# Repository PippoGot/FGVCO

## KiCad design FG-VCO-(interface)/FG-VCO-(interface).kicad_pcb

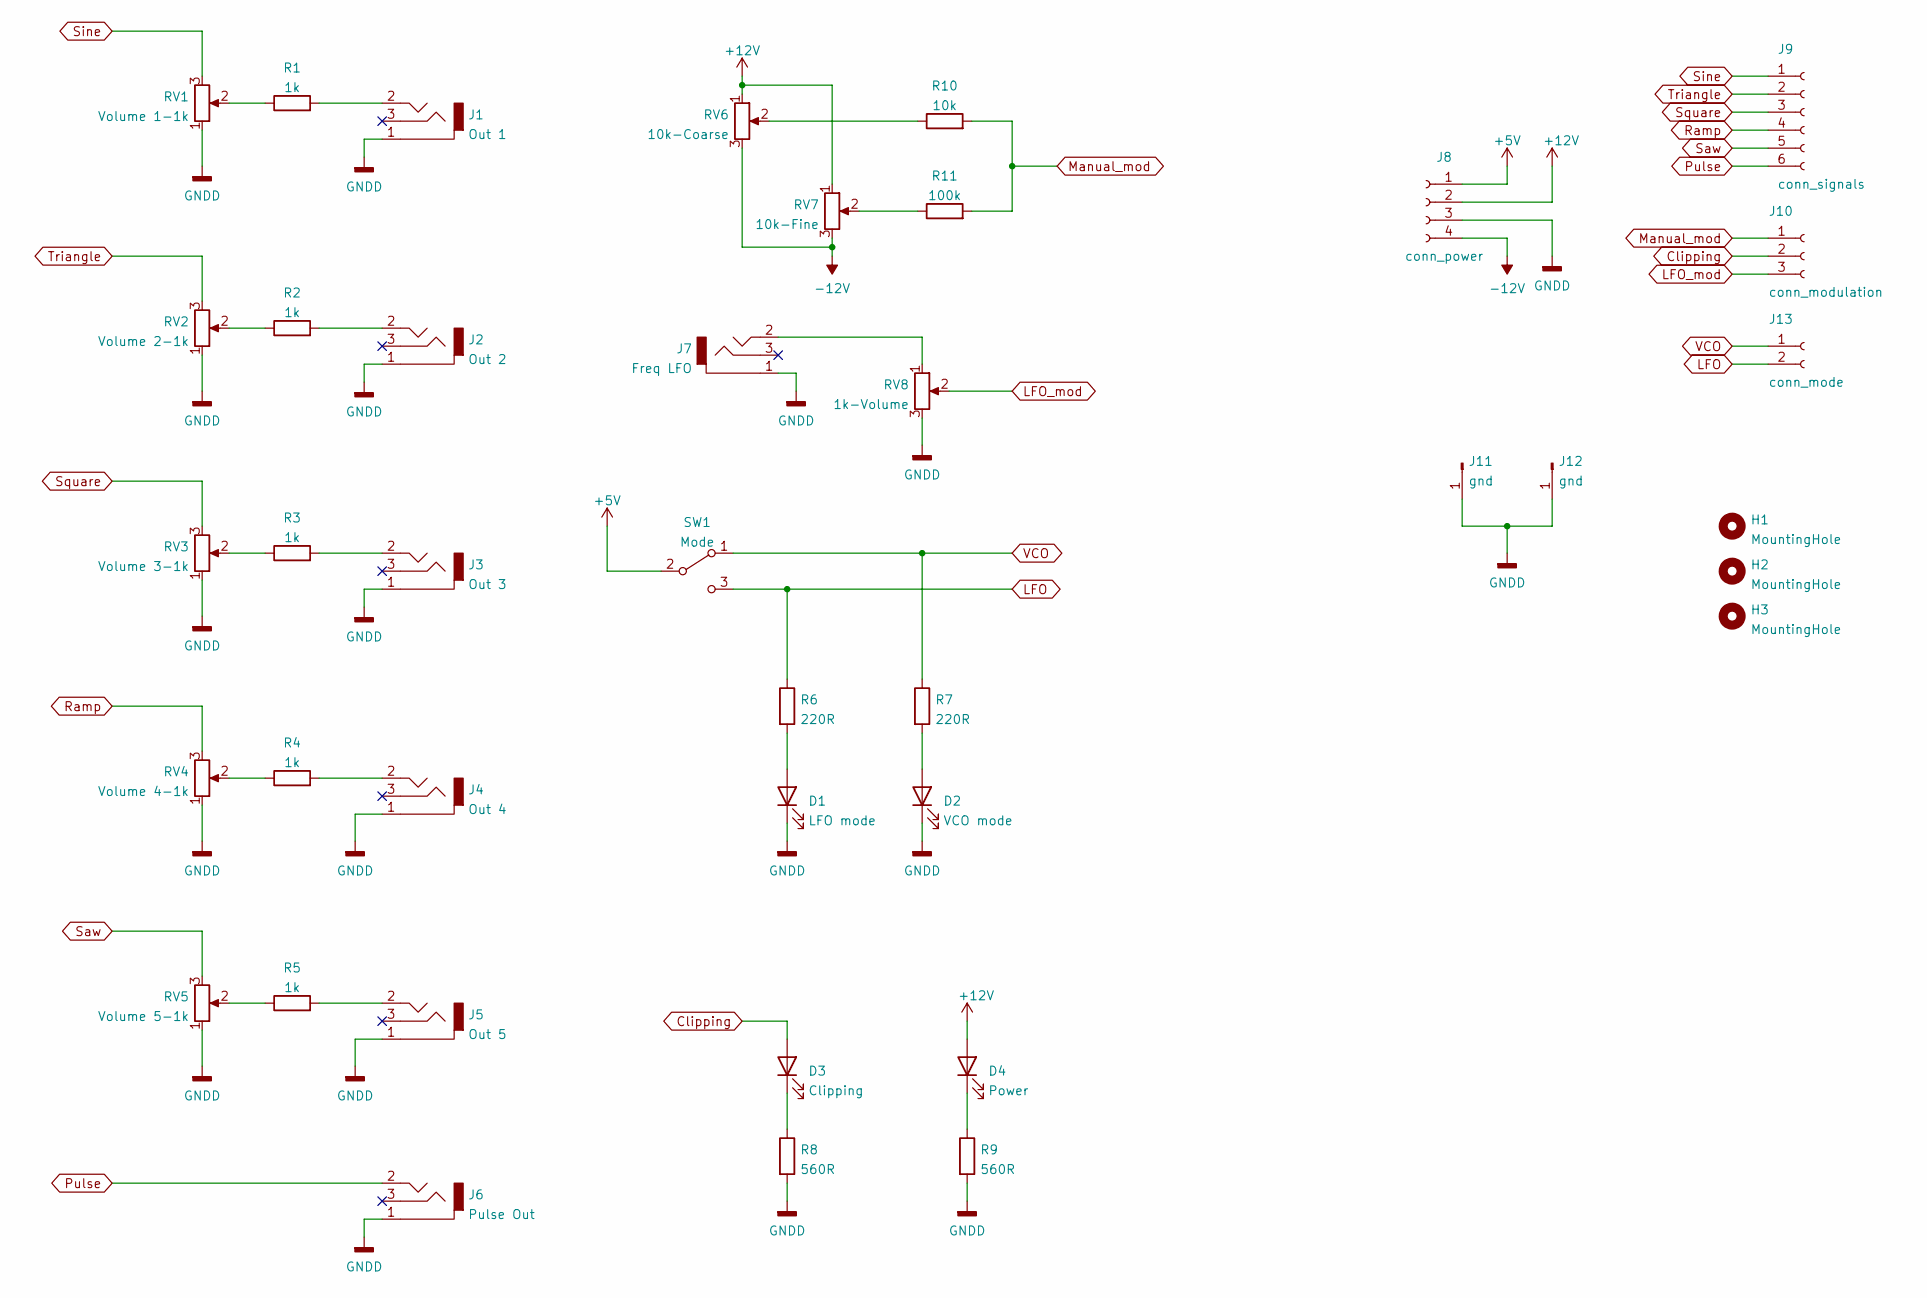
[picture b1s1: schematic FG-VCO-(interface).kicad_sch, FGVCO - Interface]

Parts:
D1: LFO mode; LED_D3.0mm_FlatTop
D2: VCO mode; LED_D3.0mm_FlatTop
D3: Clipping; LED_D3.0mm_FlatTop
D4: Power; LED_D3.0mm_FlatTop
H1, H2, H3: MountingHole; MountingHole_3.2mm_M3
J1: Out 1; PJ_301M_noGND
J2: Out 2; PJ_301M_noGND
J3: Out 3; PJ_301M_noGND
J4: Out 4; PJ_301M_noGND
J5: Out 5; PJ_301M_noGND
J6: Pulse Out; PJ_301M_noGND
J7: Freq LFO; PJ_301M_noGND
J8: conn_power; PinSocket_1x04_P2.54mm_Vertical
J9: conn_signals; PinSocket_1x06_P2.54mm_Vertical
J10: conn_modulation; PinSocket_1x03_P2.54mm_Vertical
J11, J12: gnd; PinSocket_1x01_P2.54mm_Vertical
J13: conn_mode; PinSocket_1x02_P2.54mm_Vertical
R1, R2, R3, R4, R5: 1k; R_Axial_DIN0207_L6.3mm_D2.5mm_P10.16mm_Horizontal
R6, R7: 220R; R_Axial_DIN0207_L6.3mm_D2.5mm_P10.16mm_Horizontal
R8, R9: 560R; R_Axial_DIN0207_L6.3mm_D2.5mm_P10.16mm_Horizontal
R10: 10k; R_Axial_DIN0207_L6.3mm_D2.5mm_P10.16mm_Horizontal
R11: 100k; R_Axial_DIN0207_L6.3mm_D2.5mm_P10.16mm_Horizontal
RV1: Volume 1-1k; RV-90 Potentiometer
RV2: Volume 2-1k; RV-90 Potentiometer
RV3: Volume 3-1k; RV-90 Potentiometer
RV4: Volume 4-1k; RV-90 Potentiometer
RV5: Volume 5-1k; RV-90 Potentiometer
RV6: 10k-Coarse; RV-90 Potentiometer
RV7: 10k-Fine; RV-90 Potentiometer
RV8: 1k-Volume; RV-90 Potentiometer
SW1: Mode; SPDT Switch

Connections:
+5V: J8.1, SW1.2 (B)
+12V: D4.2 (A), J8.2, RV6.1, RV7.1
-12V: J8.4, RV6.3, RV7.3
Clipping: D3.2 (A), J10.2
GNDD: D1.1 (K), D2.1 (K), J1.1, J2.1, J3.1, J4.1, J5.1, J6.1, J7.1, J8.3, J11.1, J12.1, R8.2, R9.2, RV1.1, RV2.1, RV3.1, RV4.1, RV5.1, RV8.3
LFO: J13.2, R6.1, SW1.3 (C)
LFO_mod: J10.3, RV8.2
Manual_mod: J10.1, R10.2, R11.2
unnamed: D1.2 (A), R6.2
unnamed: D2.2 (A), R7.2
unnamed: D3.1 (K), R8.1
unnamed: D4.1 (K), R9.1
unnamed: J1.2, R1.2
unnamed: J2.2, R2.2
unnamed: J3.2, R3.2
unnamed: J4.2, R4.2
unnamed: J5.2, R5.2
unnamed: J7.2, RV8.1
unnamed: R1.1, RV1.2
unnamed: R2.1, RV2.2
unnamed: R3.1, RV3.2
unnamed: R4.1, RV4.2
unnamed: R5.1, RV5.2
unnamed: R10.1, RV6.2
unnamed: R11.1, RV7.2
Pulse: J6.2, J9.6
Ramp: J9.4, RV4.3
Saw: J9.5, RV5.3
Sine: J9.1, RV1.3
Square: J9.3, RV3.3
Triangle: J9.2, RV2.3
VCO: J13.1, R7.1, SW1.1 (A)

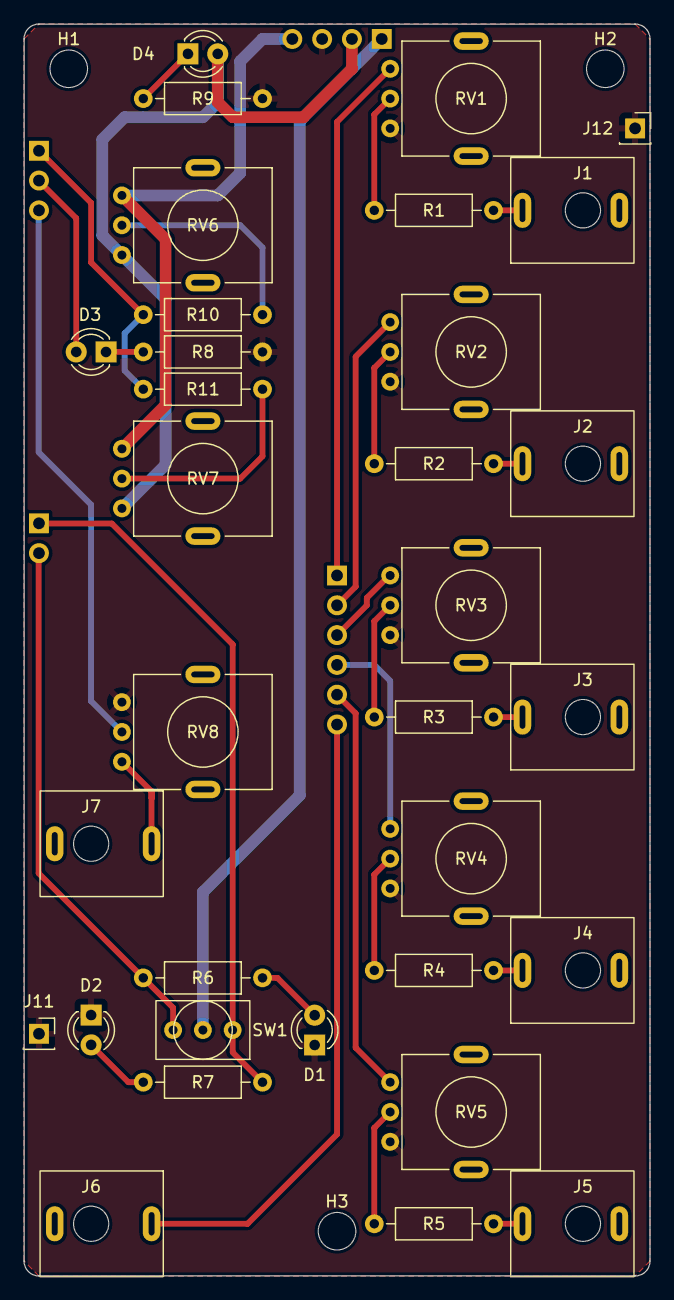
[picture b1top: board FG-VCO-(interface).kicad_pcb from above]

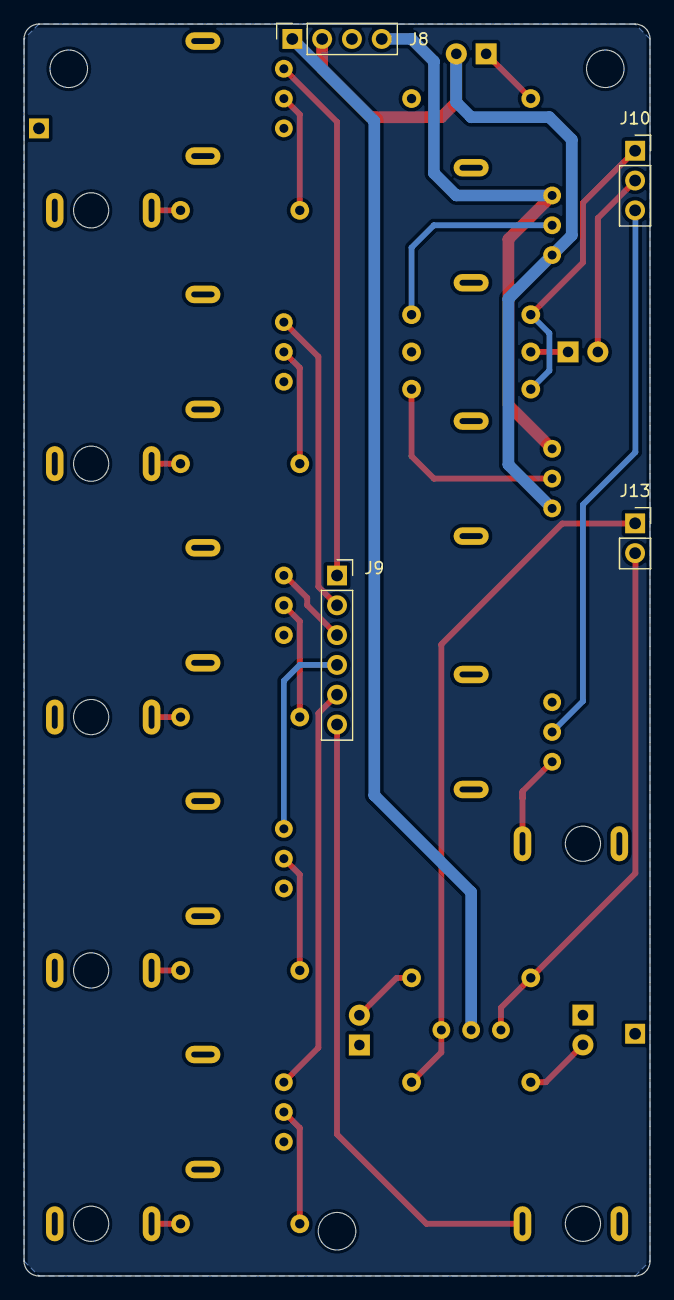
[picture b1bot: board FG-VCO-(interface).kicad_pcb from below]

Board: 2 copper layers, 53.3 x 106.7 mm, 40 parts (4 on the bottom side), 32 nets.

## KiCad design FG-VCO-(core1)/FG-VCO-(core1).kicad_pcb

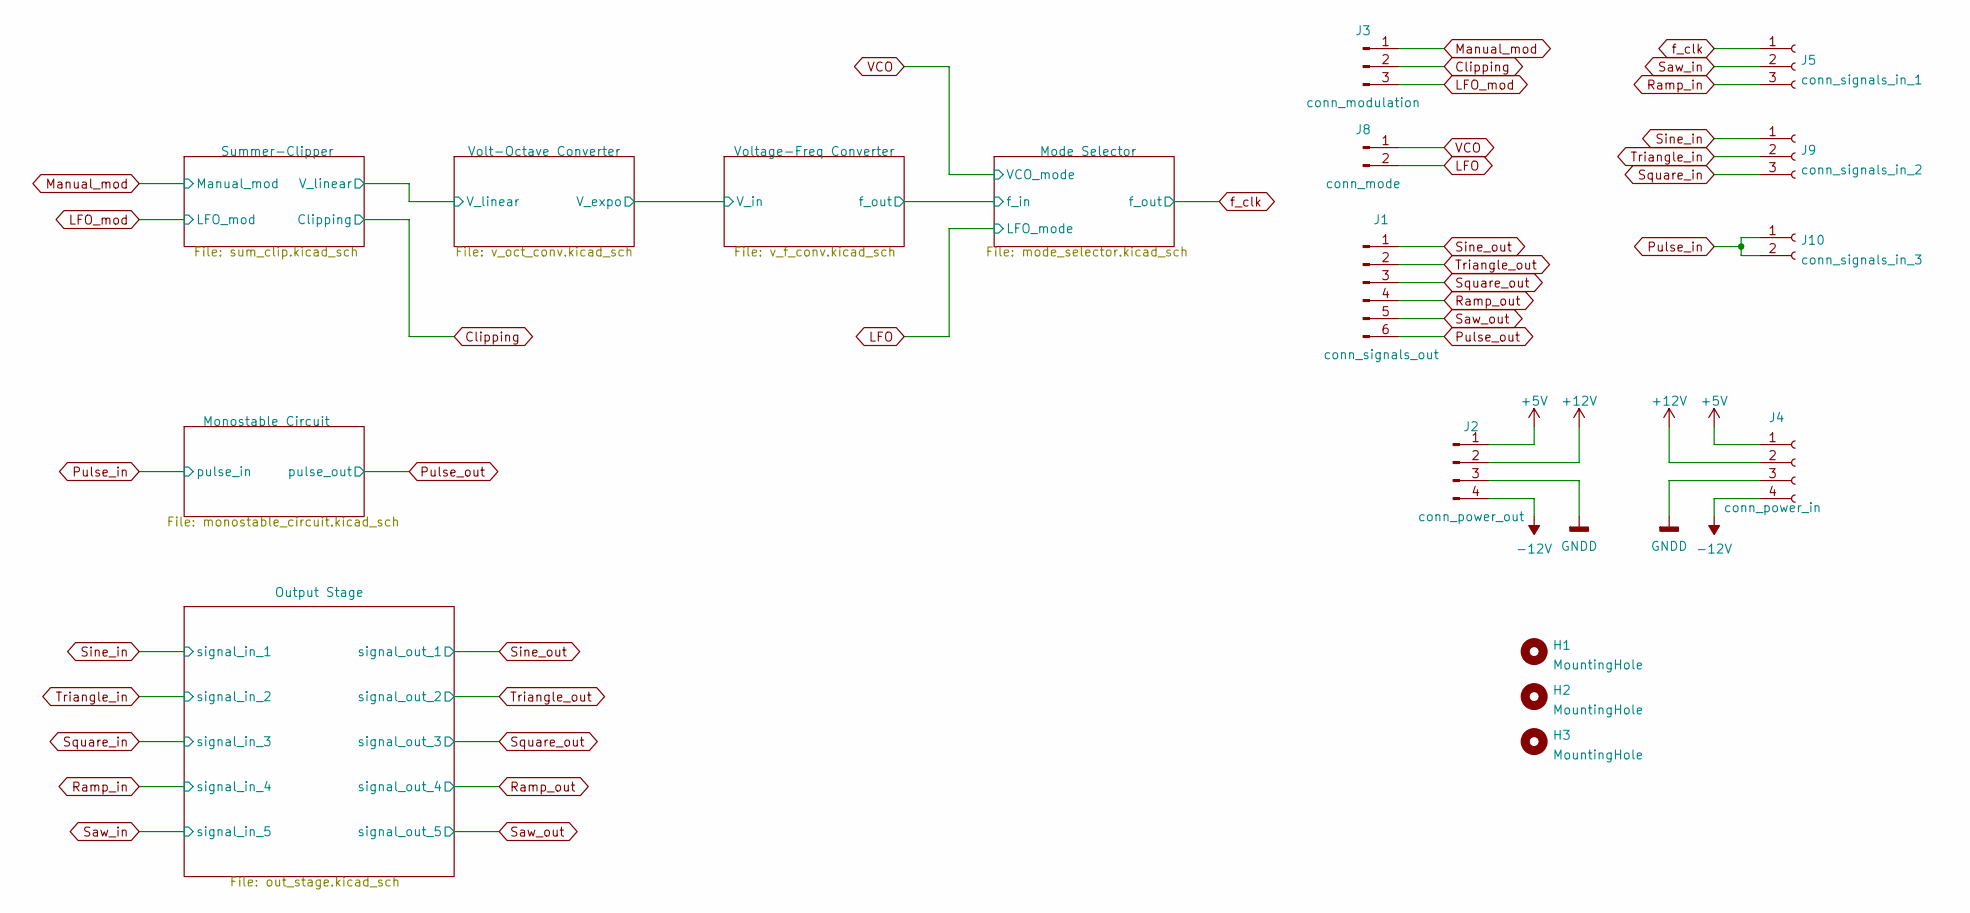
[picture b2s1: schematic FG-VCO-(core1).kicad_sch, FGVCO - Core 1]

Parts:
H1, H2, H3: MountingHole; MountingHole_3.2mm_M3
J1: conn_signals_out; PinHeader_1x06_P2.54mm_Vertical
J2: conn_power_out; PinHeader_1x04_P2.54mm_Vertical
J3: conn_modulation; PinHeader_1x03_P2.54mm_Vertical
J4: conn_power_in; PinSocket_1x04_P2.54mm_Vertical
J5: conn_signals_in_1; PinSocket_1x03_P2.54mm_Vertical
J8: conn_mode; PinHeader_1x02_P2.54mm_Vertical
J9: conn_signals_in_2; PinSocket_1x03_P2.54mm_Vertical
J10: conn_signals_in_3; PinSocket_1x02_P2.54mm_Vertical

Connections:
+5V: J2.1, J4.1; also elsewhere on the board
+12V: J2.2, J4.2; also elsewhere on the board
-12V: J2.4, J4.4; also elsewhere on the board
Clipping: J3.2; also elsewhere on the board
GNDD: J2.3, J4.3; also elsewhere on the board
LFO: J8.2; also elsewhere on the board
LFO_mod: J3.3; also elsewhere on the board
Manual_mod: J3.1; also elsewhere on the board
Pulse_in: J10.1, J10.2; also elsewhere on the board
Pulse_out: J1.6; also elsewhere on the board
Ramp_in: J5.3; also elsewhere on the board
Ramp_out: J1.4; also elsewhere on the board
Saw_in: J5.2; also elsewhere on the board
Saw_out: J1.5; also elsewhere on the board
Sine_in: J9.1; also elsewhere on the board
Sine_out: J1.1; also elsewhere on the board
Square_in: J9.3; also elsewhere on the board
Square_out: J1.3; also elsewhere on the board
Triangle_in: J9.2; also elsewhere on the board
Triangle_out: J1.2; also elsewhere on the board
VCO: J8.1; also elsewhere on the board
f_clk: J5.1; also elsewhere on the board

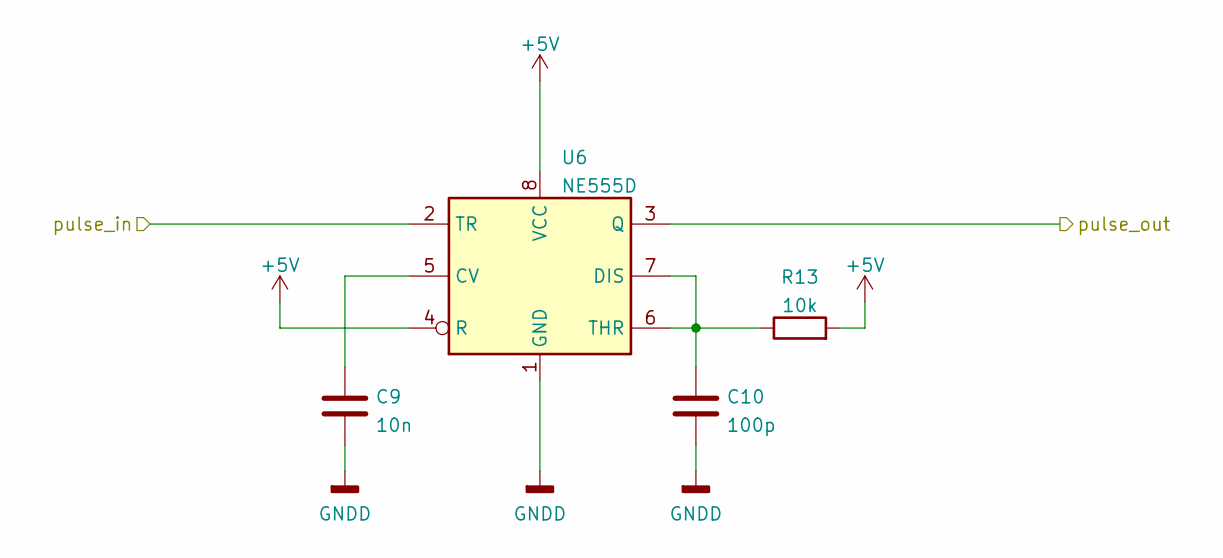
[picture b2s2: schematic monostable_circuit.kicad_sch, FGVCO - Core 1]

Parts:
C9: 10n; C_Disc_P2.54mm
C10: 100p; C_Disc_P2.54mm
R13: 10k; R_Axial_DIN0207_L6.3mm_D2.5mm_P10.16mm_Horizontal
U6: NE555D; DIP-8_central_caps

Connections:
+5V: R13.2, U6.4 (R), U6.8 (VCC); also elsewhere on the board
GNDD: C9.2, C10.2, U6.1 (GND); also elsewhere on the board
unnamed: C9.1, U6.5 (CV)
unnamed: C10.1, R13.1, U6.6 (THR), U6.7 (DIS)
Pulse_in: U6.2 (TR); also elsewhere on the board
Pulse_out: U6.3 (Q); also elsewhere on the board

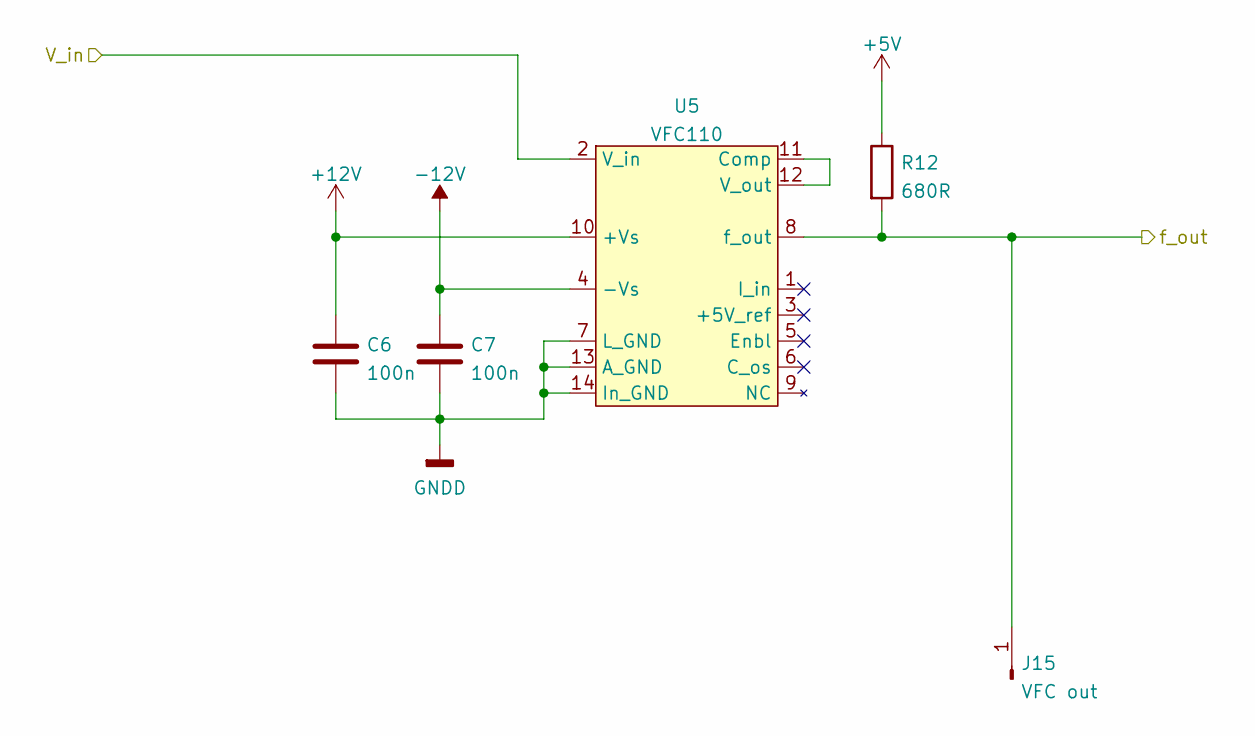
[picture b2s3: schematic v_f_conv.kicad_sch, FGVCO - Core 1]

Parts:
C6, C7: 100n; C_Disc_P2.54mm
J15: VFC out; PinHeader_1x01_P2.54mm_Vertical
R12: 680R; R_Axial_DIN0207_L6.3mm_D2.5mm_P10.16mm_Horizontal
U5: VFC110; DIP-14_central_caps

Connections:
+5V: R12.1; also elsewhere on the board
+12V: C6.2, U5.10 (+Vs); also elsewhere on the board
-12V: C7.2, U5.4 (-Vs); also elsewhere on the board
/Mode Selector/f_in: J15.1, R12.2, U5.8 (f_out); also elsewhere on the board
/Volt-Octave Converter/V_expo: U5.2 (V_in); also elsewhere on the board
GNDD: C6.1, C7.1, U5.7 (L_GND), U5.13 (A_GND), U5.14 (In_GND); also elsewhere on the board
unnamed: U5.11 (Comp), U5.12 (V_out)

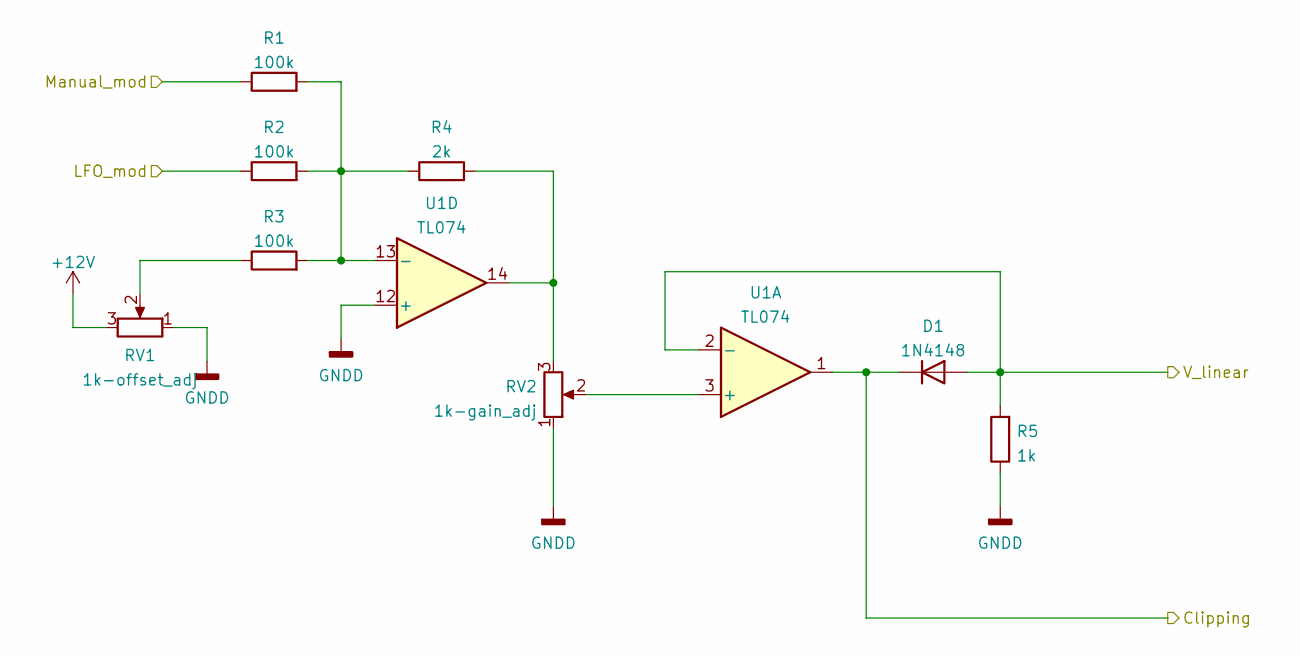
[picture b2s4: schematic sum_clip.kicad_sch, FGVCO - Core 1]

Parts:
D1: 1N4148; D_DO-35_SOD27_P7.62mm_Horizontal
R1, R2, R3: 100k; R_Axial_DIN0207_L6.3mm_D2.5mm_P10.16mm_Horizontal
R4: 2k; R_Axial_DIN0207_L6.3mm_D2.5mm_P10.16mm_Horizontal
R5: 1k; R_Axial_DIN0207_L6.3mm_D2.5mm_P10.16mm_Horizontal
RV1: 1k-offset_adj; Potentiometer_Vishay_T73YP_Vertical
RV2: 1k-gain_adj; Potentiometer_Bourns_3296W_Vertical
U1: TL074; DIP-14_central_caps

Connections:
+12V: RV1.3; also elsewhere on the board
/Summer-Clipper/V_linear: D1.2 (A), R5.2, U1.2 (-); also elsewhere on the board
Clipping: D1.1 (K), U1.1; also elsewhere on the board
GNDD: R5.1, RV1.1, RV2.1, U1.12 (+); also elsewhere on the board
LFO_mod: R2.1; also elsewhere on the board
Manual_mod: R1.1; also elsewhere on the board
unnamed: R1.2, R2.2, R3.2, R4.1, U1.13 (-)
unnamed: R3.1, RV1.2
unnamed: R4.2, RV2.3, U1.14
unnamed: RV2.2, U1.3 (+)

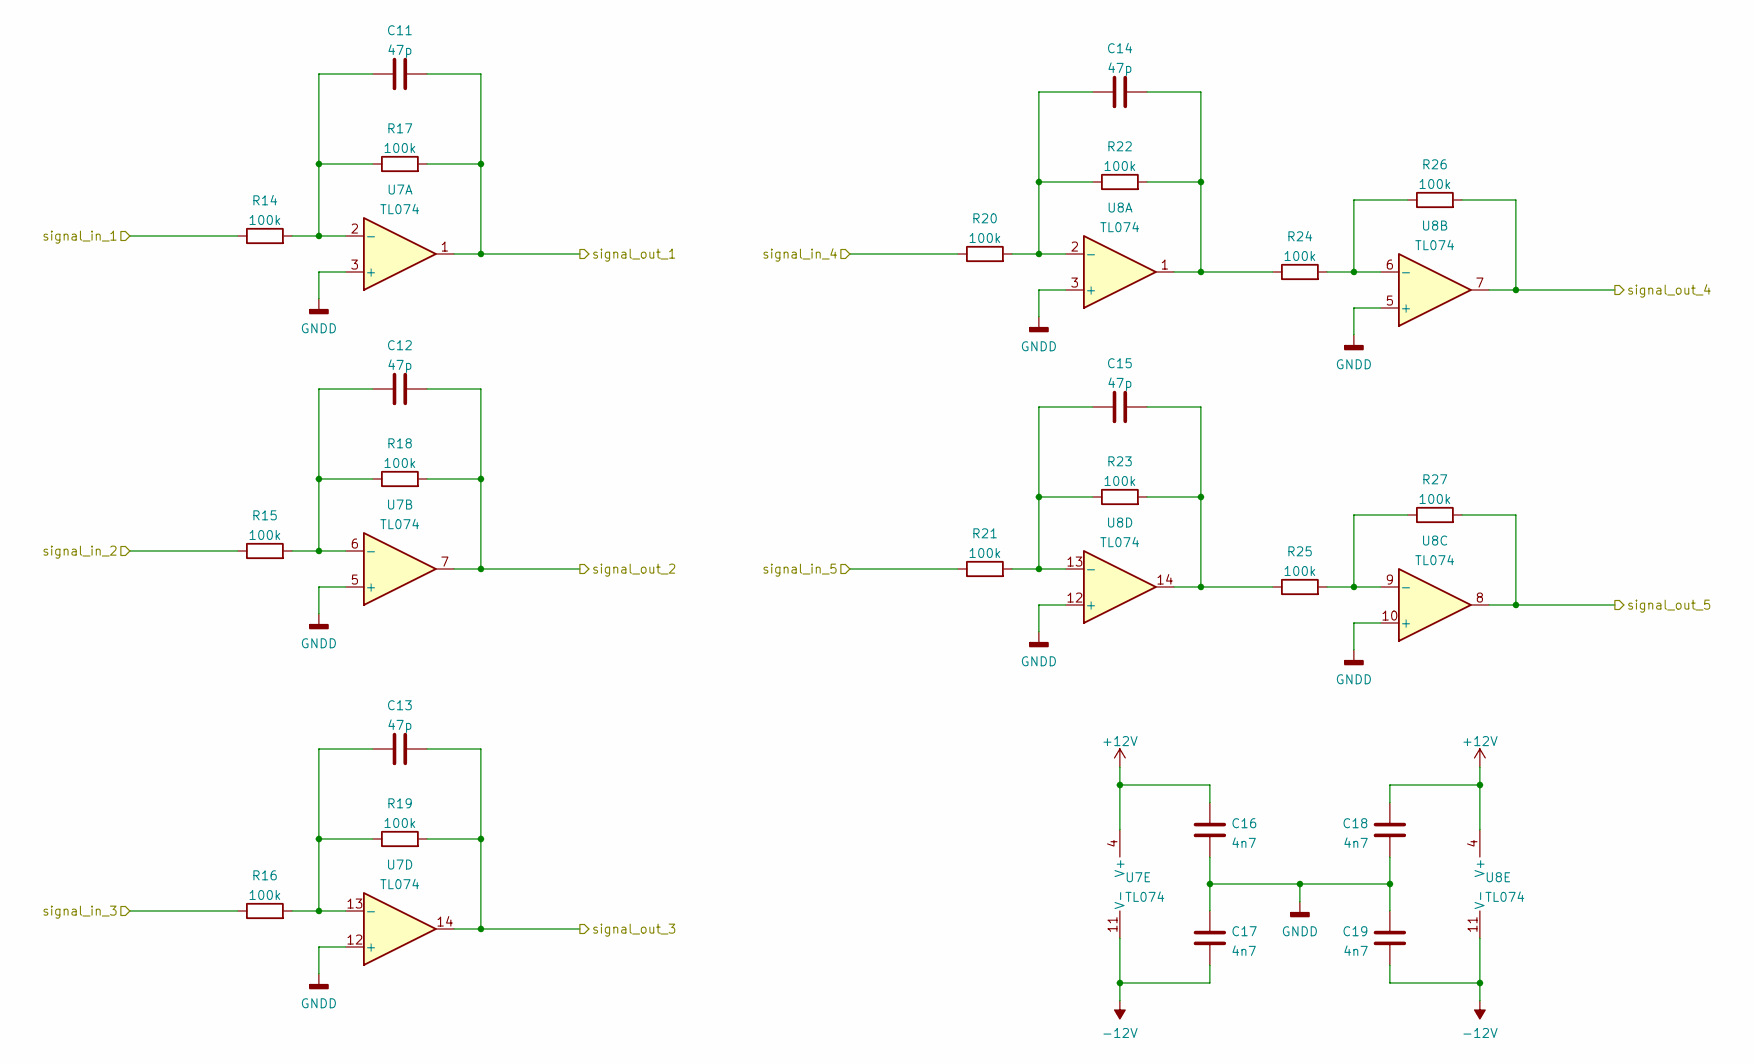
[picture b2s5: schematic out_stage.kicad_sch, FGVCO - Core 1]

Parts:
C11, C12, C13, C14, C15: 47p; C_Disc_P2.54mm
C16, C17, C18, C19: 4n7; C_Disc_P2.54mm
R14, R15, R16, R17, R18, R19, R20, R21, R22, R23, R24, R25, R26, R27: 100k; R_Axial_DIN0207_L6.3mm_D2.5mm_P10.16mm_Horizontal
U7, U8: TL074; DIP-14_central_caps

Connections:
+12V: C16.1, C18.1, U7.4 (V+), U8.4 (V+); also elsewhere on the board
-12V: C17.2, C19.2, U7.11 (V-), U8.11 (V-); also elsewhere on the board
GNDD: C16.2, C17.1, C18.2, C19.1, U7.3 (+), U7.5 (+), U7.12 (+), U8.3 (+), U8.5 (+), U8.10 (+), U8.12 (+); also elsewhere on the board
unnamed: C11.1, R14.2, R17.1, U7.2 (-)
unnamed: C12.1, R15.2, R18.1, U7.6 (-)
unnamed: C13.1, R16.2, R19.1, U7.13 (-)
unnamed: C14.1, R20.2, R22.1, U8.2 (-)
unnamed: C14.2, R22.2, R24.1, U8.1
unnamed: C15.1, R21.2, R23.1, U8.13 (-)
unnamed: C15.2, R23.2, R25.1, U8.14
unnamed: R24.2, R26.1, U8.6 (-)
unnamed: R25.2, R27.1, U8.9 (-)
Ramp_in: R20.1; also elsewhere on the board
Ramp_out: R26.2, U8.7; also elsewhere on the board
Saw_in: R21.1; also elsewhere on the board
Saw_out: R27.2, U8.8; also elsewhere on the board
Sine_in: R14.1; also elsewhere on the board
Sine_out: C11.2, R17.2, U7.1; also elsewhere on the board
Square_in: R16.1; also elsewhere on the board
Square_out: C13.2, R19.2, U7.14; also elsewhere on the board
Triangle_in: R15.1; also elsewhere on the board
Triangle_out: C12.2, R18.2, U7.7; also elsewhere on the board

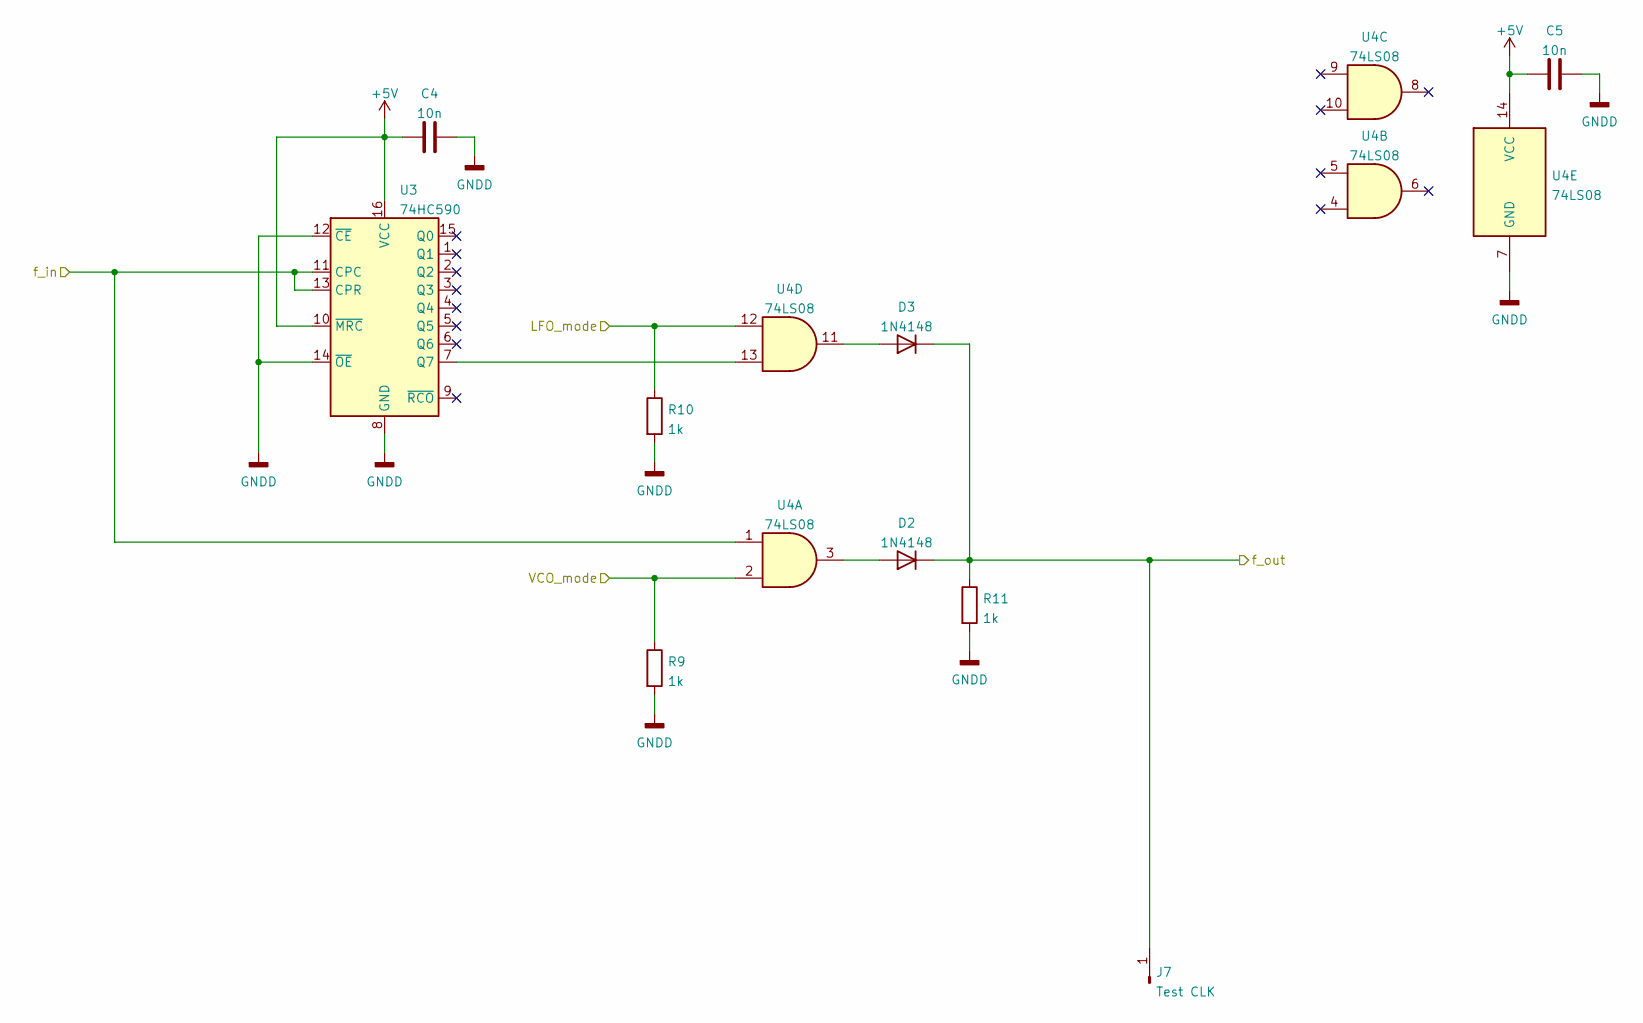
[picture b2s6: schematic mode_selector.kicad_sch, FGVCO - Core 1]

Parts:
C4, C5: 10n; C_Disc_P2.54mm
D2, D3: 1N4148; D_DO-35_SOD27_P7.62mm_Horizontal
J7: Test CLK; PinHeader_1x01_P2.54mm_Vertical
R9, R10, R11: 1k; R_Axial_DIN0207_L6.3mm_D2.5mm_P10.16mm_Horizontal
U3: 74HC590; DIP-16_central_caps
U4: 74LS08; DIP-14_central_caps

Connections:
+5V: C4.2, C5.2, U3.10 (~MRC), U3.16 (VCC), U4.14 (VCC); also elsewhere on the board
/Mode Selector/f_in: U3.11 (CPC), U3.13 (CPR), U4.1; also elsewhere on the board
GNDD: C4.1, C5.1, R9.2, R10.2, R11.2, U3.8 (GND), U3.12 (~CE), U3.14 (~OE), U4.7 (GND); also elsewhere on the board
LFO: R10.1, U4.12; also elsewhere on the board
unnamed: D2.2 (A), U4.3
unnamed: D3.2 (A), U4.11
unnamed: U3.7 (Q7), U4.13
VCO: R9.1, U4.2; also elsewhere on the board
f_clk: D2.1 (K), D3.1 (K), J7.1, R11.1; also elsewhere on the board

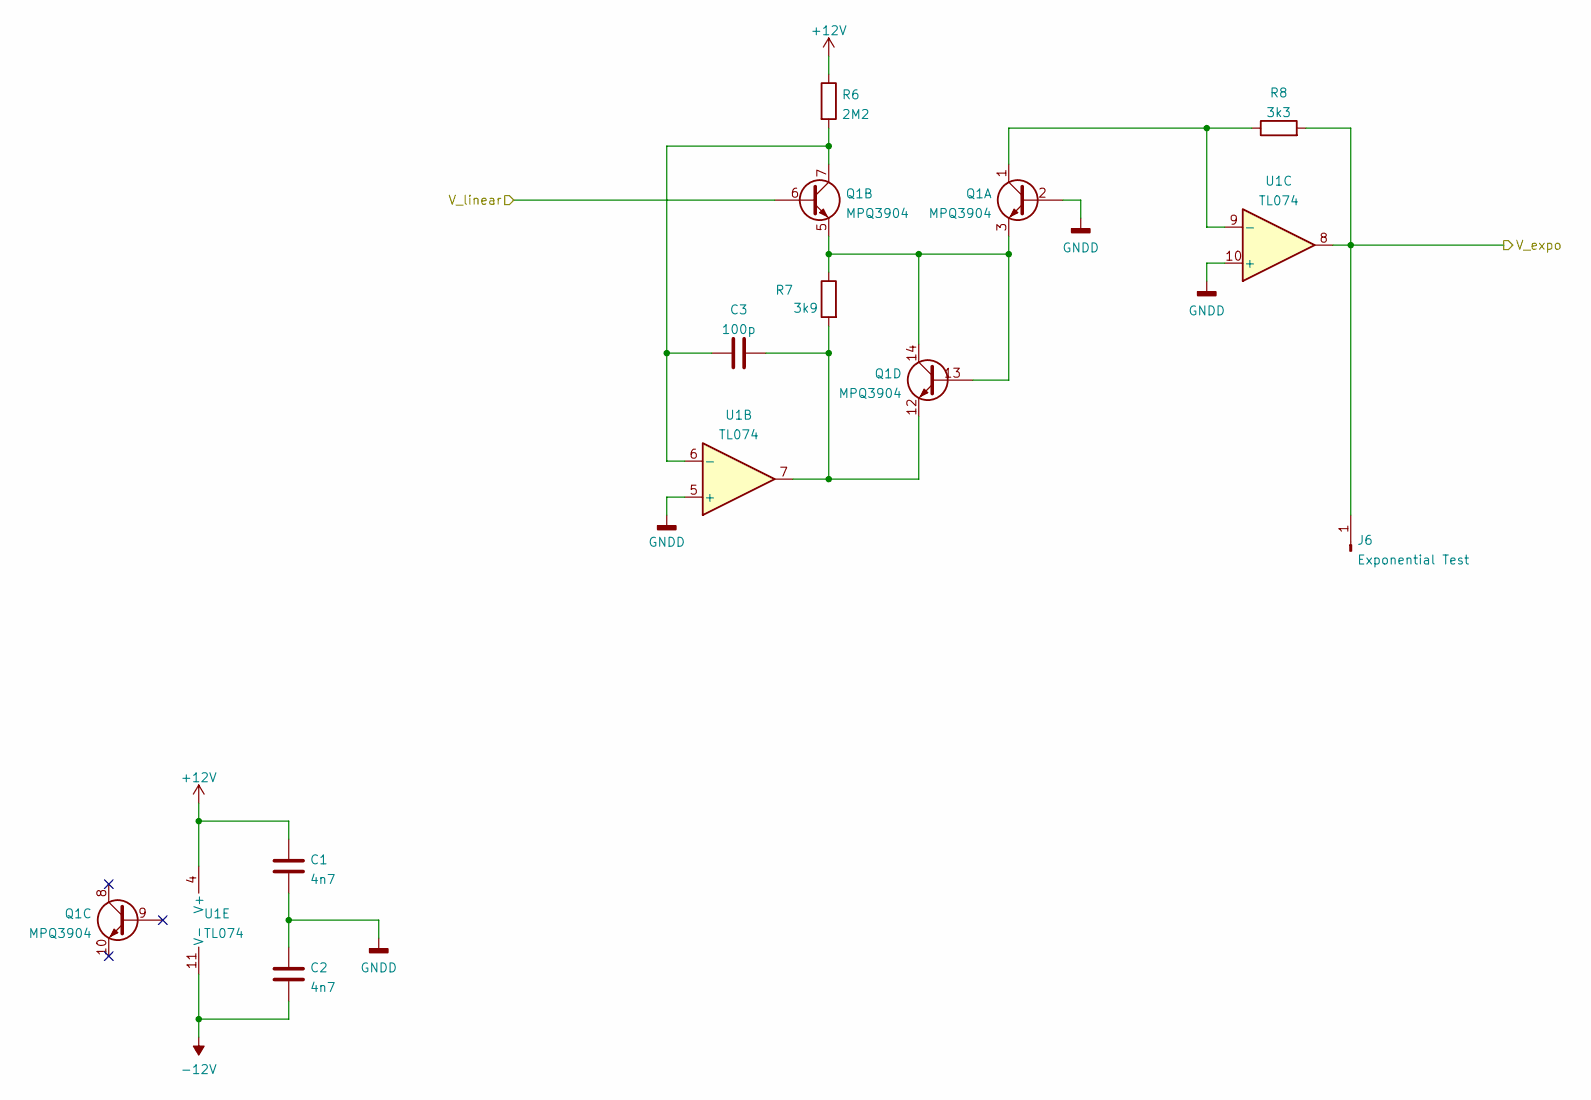
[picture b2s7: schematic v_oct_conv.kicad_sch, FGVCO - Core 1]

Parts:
C1, C2: 4n7; C_Disc_P2.54mm
C3: 100p; C_Disc_P2.54mm
J6: Exponential Test; PinHeader_1x01_P2.54mm_Vertical
Q1: MPQ3904; DIP-14_central_caps
R6: 2M2; R_Axial_DIN0207_L6.3mm_D2.5mm_P10.16mm_Horizontal
R7: 3k9; R_Axial_DIN0207_L6.3mm_D2.5mm_P10.16mm_Horizontal
R8: 3k3; R_Axial_DIN0207_L6.3mm_D2.5mm_P10.16mm_Horizontal
U1: TL074; DIP-14_central_caps

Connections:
+12V: C1.1, R6.1, U1.4 (V+); also elsewhere on the board
-12V: C2.2, U1.11 (V-); also elsewhere on the board
/Summer-Clipper/V_linear: Q1.6; also elsewhere on the board
/Volt-Octave Converter/V_expo: J6.1, R8.2, U1.8; also elsewhere on the board
GNDD: C1.2, C2.1, Q1.2, U1.5 (+), U1.10 (+); also elsewhere on the board
unnamed: C3.1, Q1.7, R6.2, U1.6 (-)
unnamed: C3.2, Q1.12, R7.2, U1.7
unnamed: Q1.1, R8.1, U1.9 (-)
unnamed: Q1.3, Q1.5, Q1.13, Q1.14, R7.1

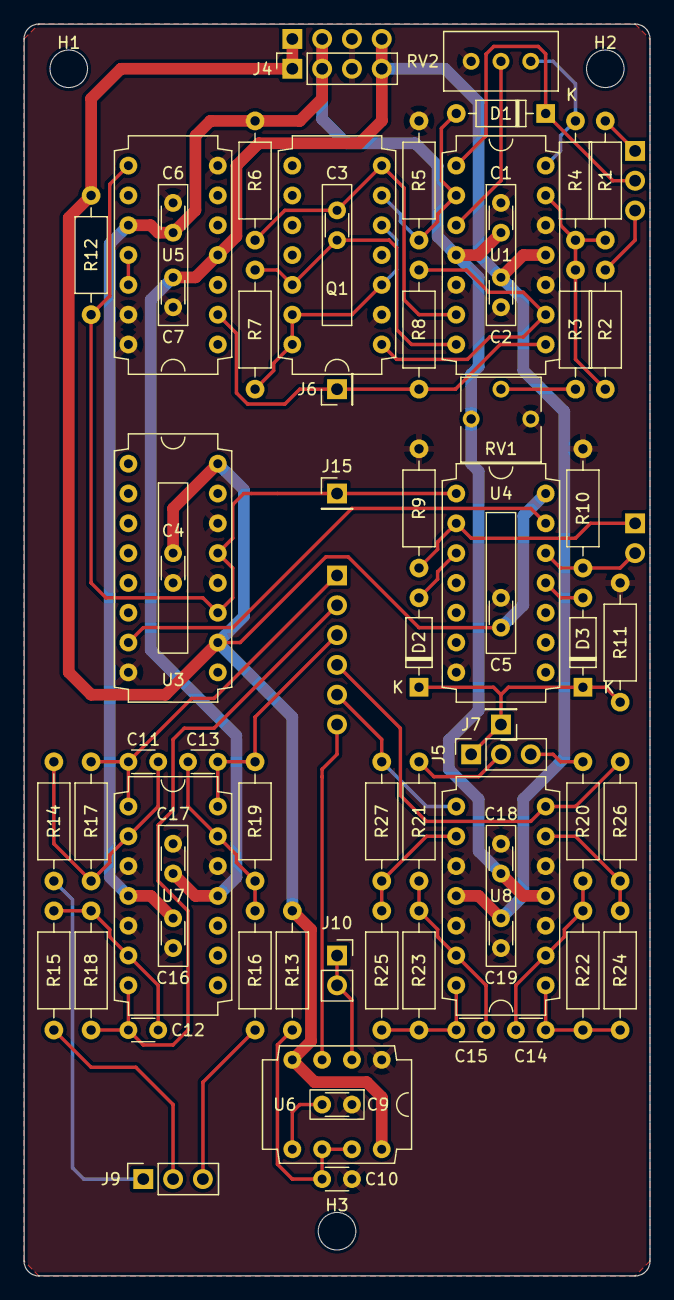
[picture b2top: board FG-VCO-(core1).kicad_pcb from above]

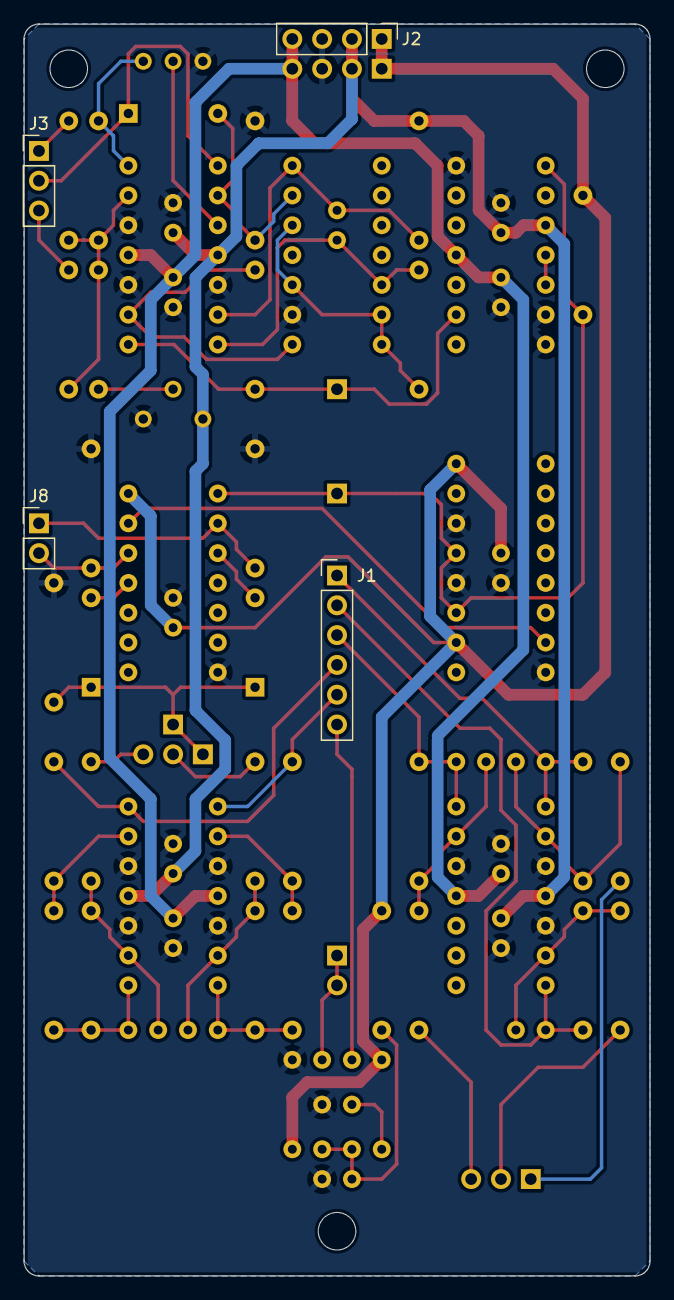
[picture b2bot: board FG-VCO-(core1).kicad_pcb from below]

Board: 2 copper layers, 53.3 x 106.7 mm, 72 parts (4 on the bottom side), 48 nets.
